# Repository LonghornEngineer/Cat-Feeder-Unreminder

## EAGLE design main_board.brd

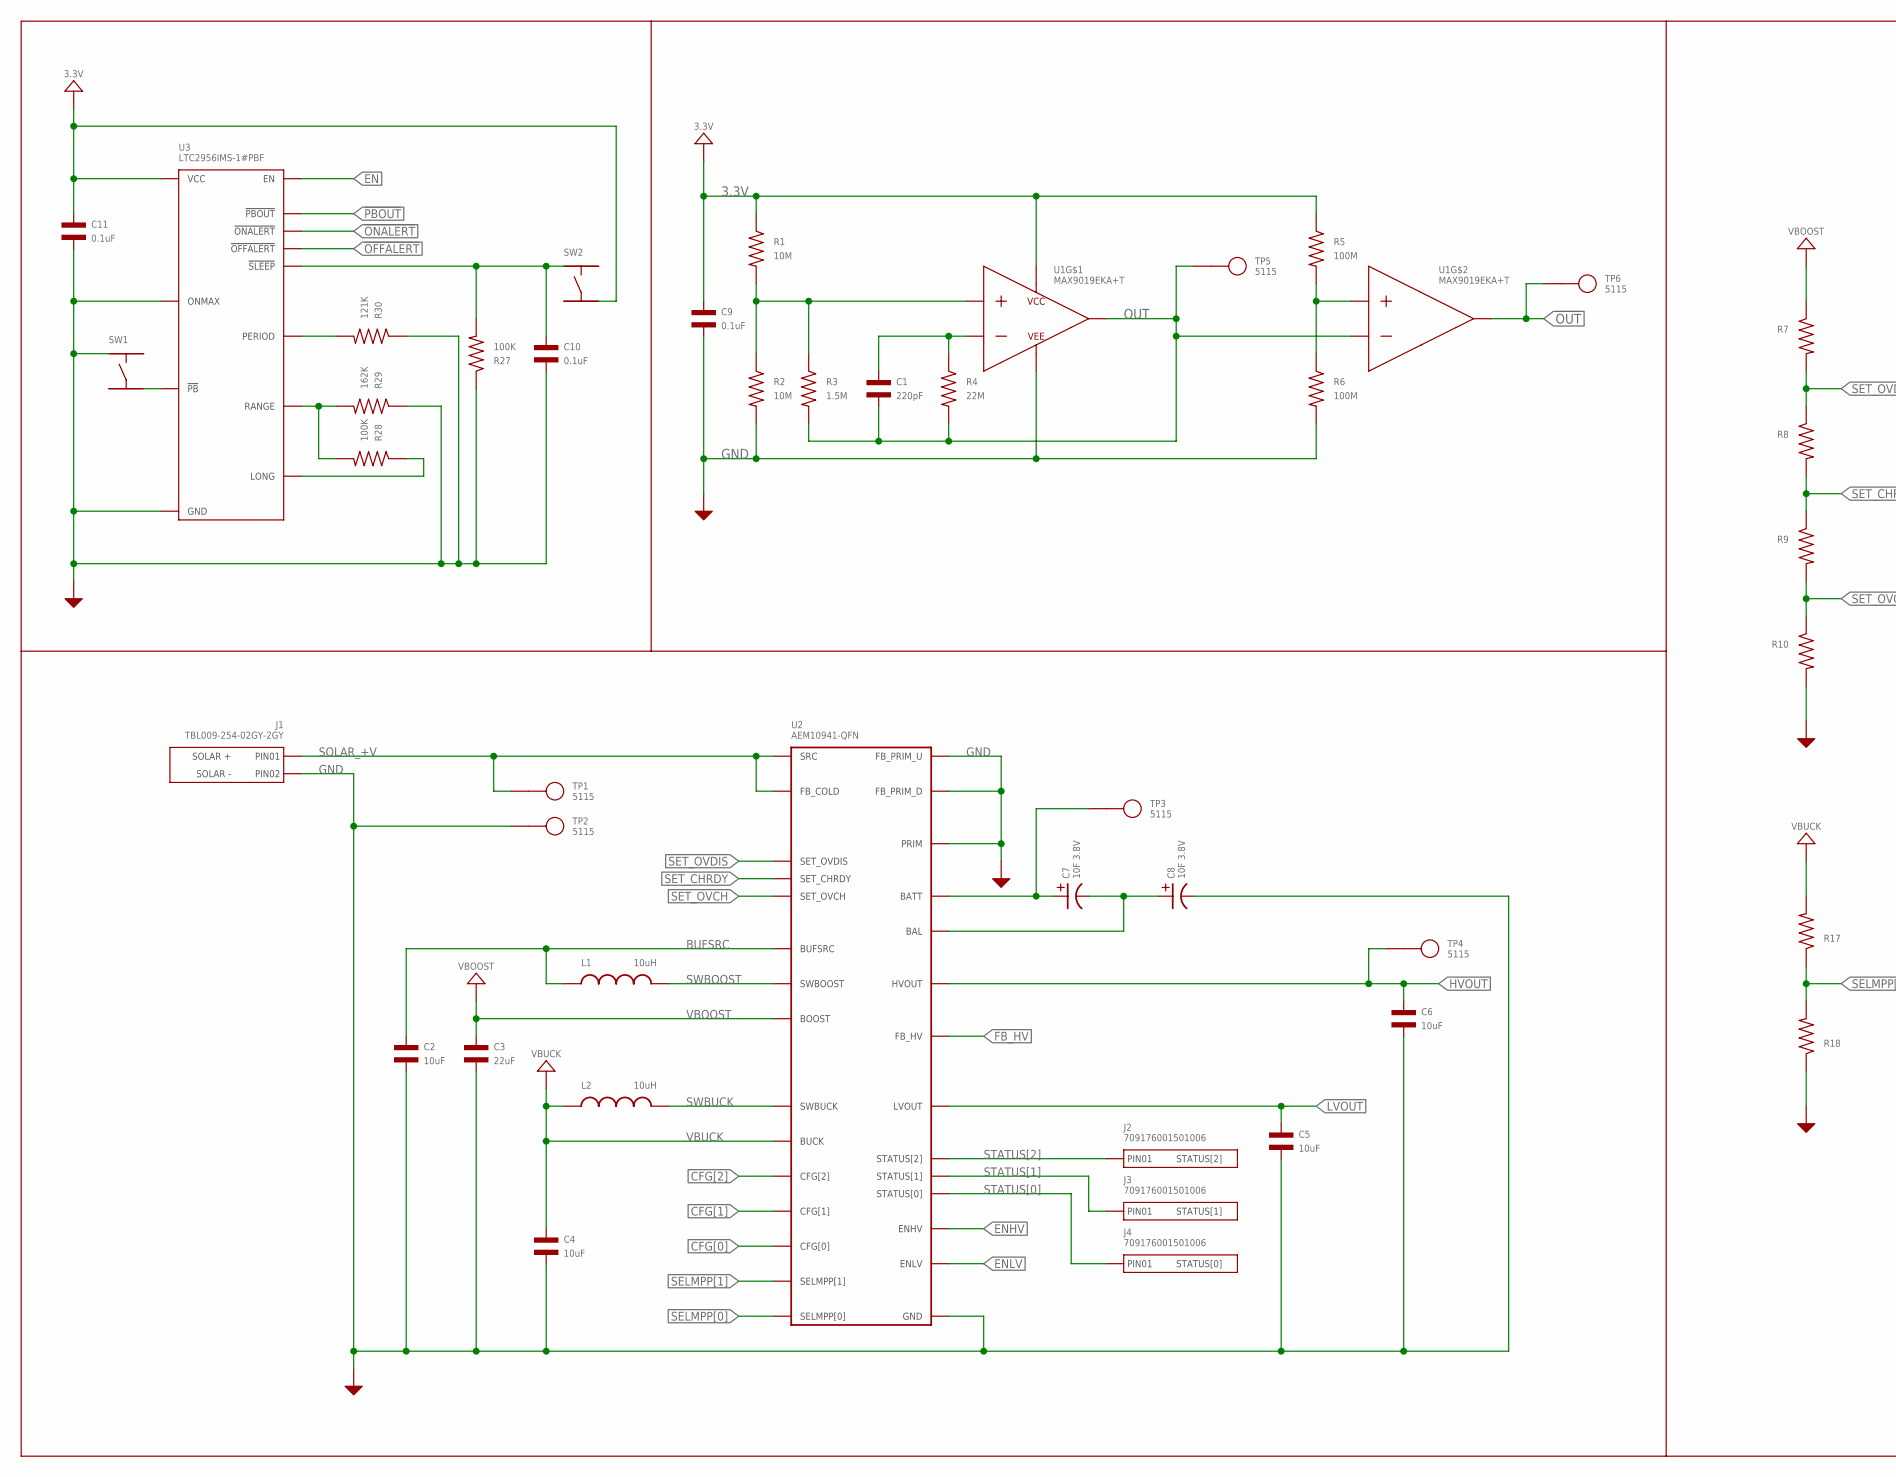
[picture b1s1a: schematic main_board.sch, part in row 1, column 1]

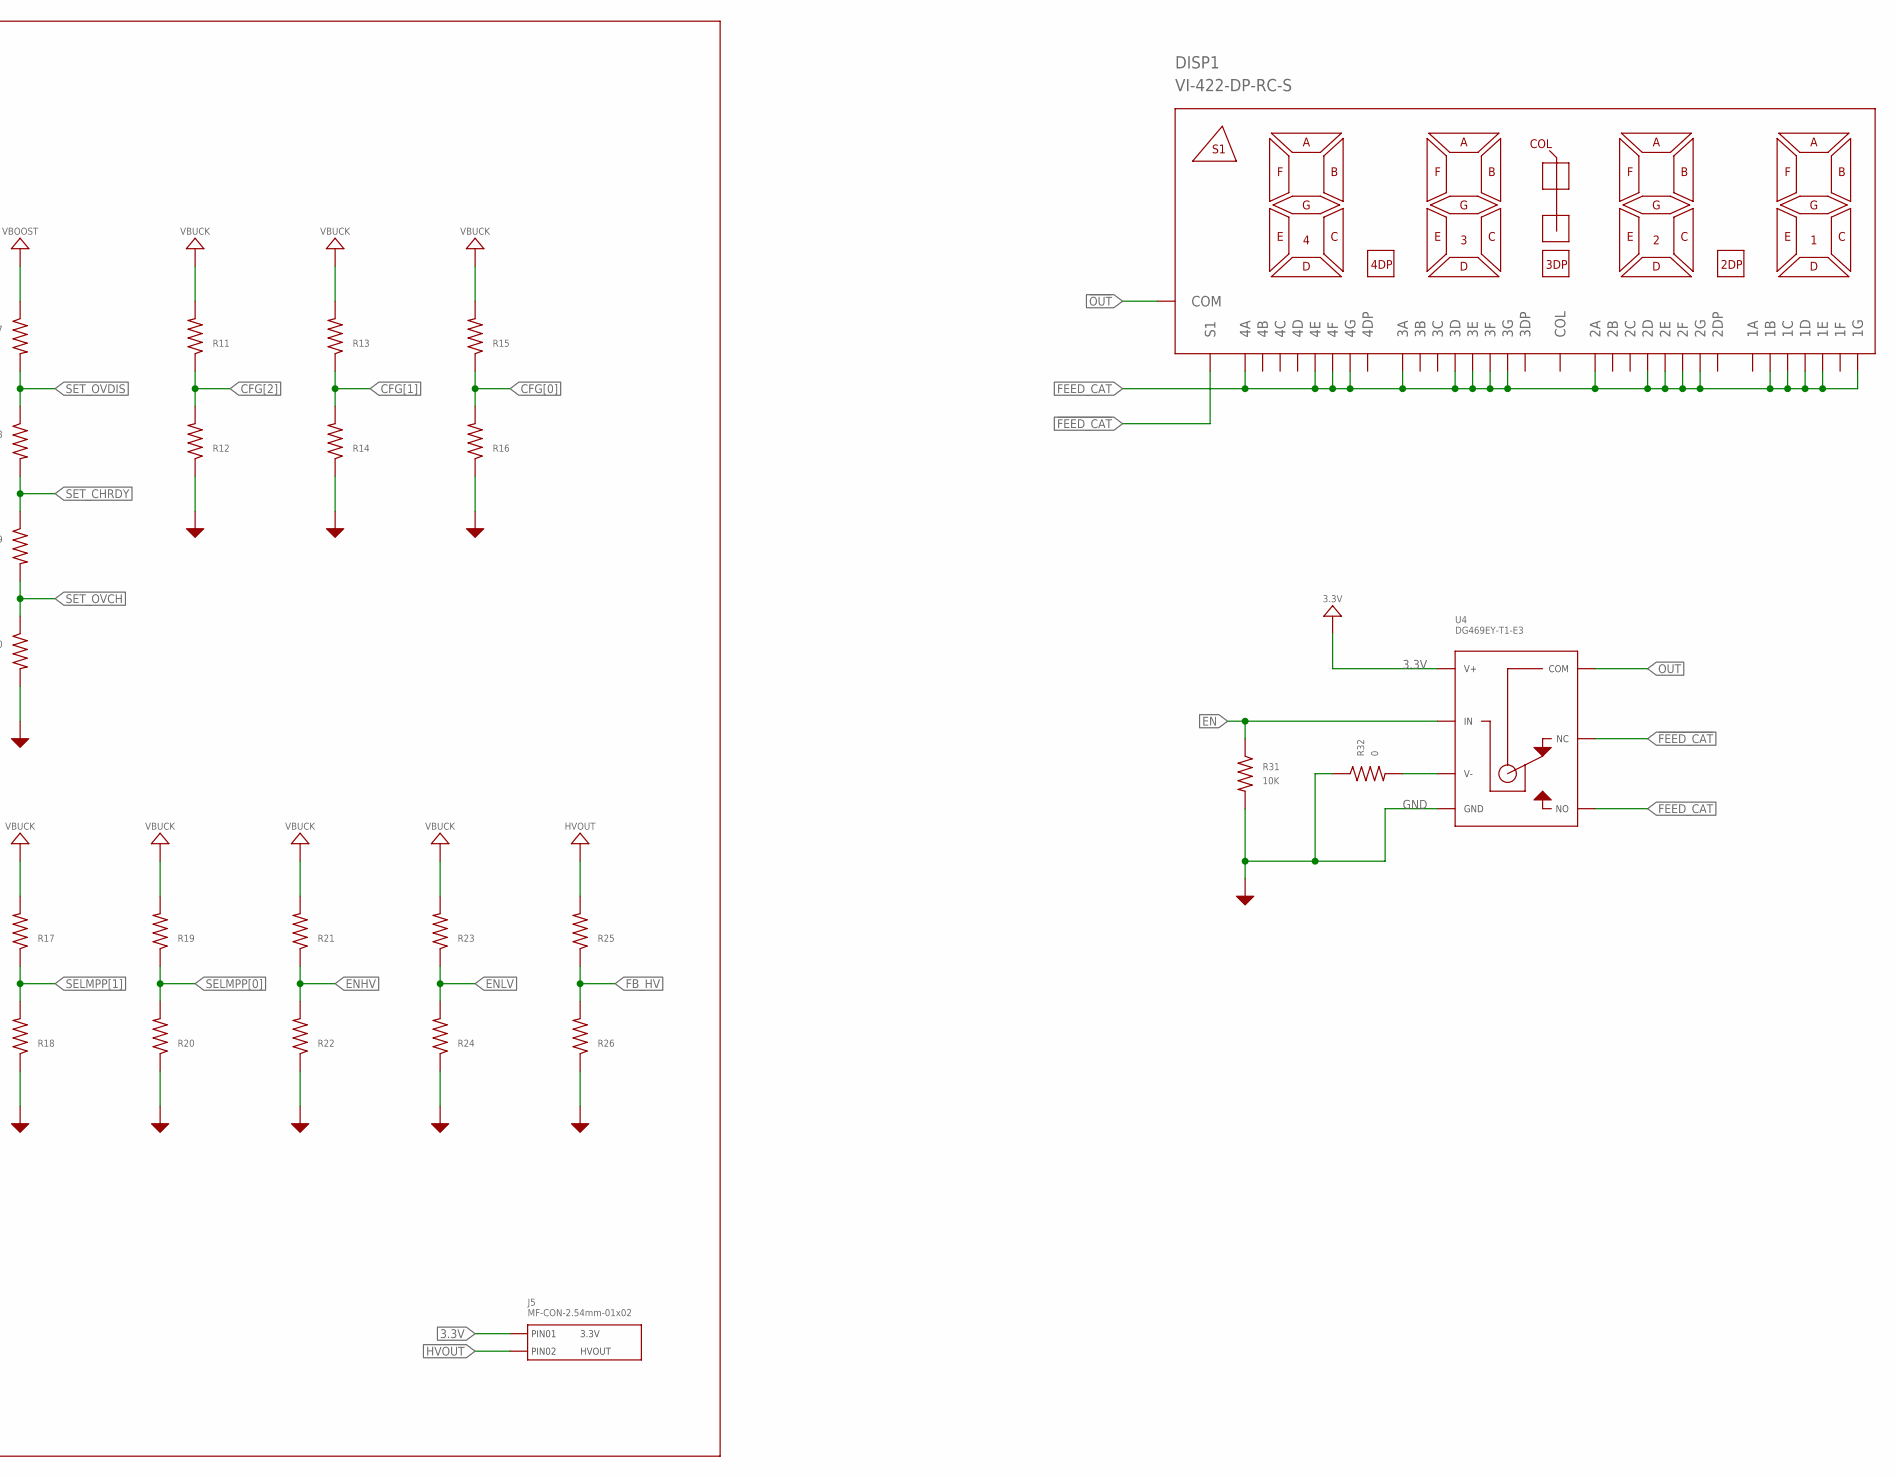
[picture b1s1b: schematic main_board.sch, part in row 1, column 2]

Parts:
C1: 220pF; C0805
C2, C4, C5, C6: 10uF; C0603; MPN C1608X5R1A106M080AC
C3: 22uF; C0603; MPN GRM188R61A226ME15D
C7, C8: 10F 3.8V; 12.5MM_CAP_PTH; MPN HSL0814-3R8106-R
C9, C10, C11: 0.1uF; C0603
DISP1: VI-422-DP-RC-S
J1: TBL009-254-02GY-2GY
J2, J3, J4: 709176001501006
J5: MF-CON-2.54mm-01x02; PTH_2.54MM_01X02
L1: 10uH; LPS4012; MPN LPS4012-103MRC
L2: 10uH; 0603; MPN MLZ1608M100WT
R1, R2: 10M; R0805
R3: 1.5M; R0805
R4: 22M; R0805
R5, R6: 100M; R0805
R7, R8, R9, R10, R11, R12, R13, R14, R15, R16, R17, R18, R19, R20, R21, R22, R23, R24, R25, R26: RESISTOR_0805; R0805
R27: 100K; R0805
R28: 100K; R0805; MPN ERA-3ARB104V
R29: 162K; R0805; MPN ERA-3AEB1623V
R30: 121K; R0805; MPN ERA-3AEB1213V
R31: 10K; R0805
R32: 0; R0805
SW1, SW2: TACT_4.2MM; TACT4.2MM; MPN PTS810 SJM 250 SMTR LFS
TP1, TP2, TP3, TP4, TP5, TP6: 5115; KEYSTONE_5115-5119
U1: MAX9019EKA+T
U2: AEM10941-QFN; AEM10941_QFN-28
U3: LTC2956IMS-1#PBF; LTC2956_MSOP-12
U4: DG469EY-T1-E3; DG469_SOIC-8

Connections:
3.3V: C9.P$1, C11.P$1, J5.P$1 (PIN1), R1.P$1, R5.P$1, SW2.P$4, U1.P$8 (VCC), U3.P$5 (VCC), U4.P$4 (V+)
!FEED_CAT: DISP1.P$38 (S1), U4.P$2 (NC)
!OFFALERT: U3.P$10 (!OFFALERT)
!ONALERT: U3.P$12 (!ONALERT)
!OUT: DISP1.P$1 (COM), DISP1.P$40 (COM), TP6.P$1, U1.P$7 (OUTPUT_2)
!PB: SW1.P$4, U3.P$7 (!PB)
!PBOUT: U3.P$9 (!PBOUT)
!SLEEP: C10.P$1, R27.P$2, SW2.P$1, U3.P$11 (!SLEEP)
BAL: C7.NEG, C8.POS, U2.P$15 (BAL)
BATT: C7.POS, TP3.P$1, U2.P$16 (BATT)
BUFSRC: C2.P$1, L1.P$2, U2.P$27 (BUFSRC)
CFG[0]: R15.P$1, R16.P$2, U2.P$6 (CFG[0])
CFG[1]: R13.P$1, R14.P$2, U2.P$5 (CFG[1])
CFG[2]: R11.P$1, R12.P$2, U2.P$4 (CFG[2])
EN: R31.P$1, U3.P$8 (EN), U4.P$6 (IN)
ENHV: R21.P$1, R22.P$2, U2.P$12 (ENHV)
ENLV: R23.P$1, R24.P$2, U2.P$18 (ENLV)
FB_HV: R25.P$1, R26.P$2, U2.P$13 (FB_HV)
FEED_CAT: DISP1.P$5 (4E), DISP1.P$9 (3E), DISP1.P$10 (3D), DISP1.P$13 (2E), DISP1.P$14 (2D), DISP1.P$17 (1E), DISP1.P$18 (1D), DISP1.P$19 (1C), DISP1.P$20 (1B), DISP1.P$23 (1G), DISP1.P$25 (2A), DISP1.P$26 (2F), DISP1.P$27 (2G), DISP1.P$30 (3A), DISP1.P$31 (3F), DISP1.P$32 (3G), DISP1.P$35 (4A), DISP1.P$36 (4F), DISP1.P$37 (4G), U4.P$8 (NO)
GND: C2.P$2, C3.P$2, C4.P$2, C5.P$2, C6.P$2, C8.NEG, C9.P$2, C10.P$2, C11.P$2, J1.2A (PIN2), J1.2B (PIN2), R2.P$2, R6.P$2, R10.P$2, R12.P$1, R14.P$1, R16.P$1, R18.P$1, R20.P$1, R22.P$1, R24.P$1, R26.P$1, R27.P$1, R29.P$1, R30.P$1, R31.P$2, R32.P$1, SW1.P$1, TP2.P$1, U1.P$4 (VEE), U2.P$9 (FB_PRIM_D), U2.P$10 (FB_PRIM_U), U2.P$17 (PRIM), U2.P$29 (GND), U3.P$1 (ONMAX), U3.P$6 (GND), U4.P$3 (GND)
HVOUT: C6.P$1, J5.P$2 (PIN2), R25.P$2, TP4.P$1, U2.P$14 (HVOUT)
LONG: R28.P$1, U3.P$2 (LONG)
LVOUT: C5.P$1, U2.P$11 (LVOUT)
unnamed: R1.P$2, R2.P$1, R3.P$1, U1.P$3 (INPUT_1+)
unnamed: R5.P$2, R6.P$1, U1.P$5 (INPUT_2+)
unnamed: C1.P$1, R4.P$1, U1.P$2 (INPUT_1-)
unnamed: R32.P$2, U4.P$7 (V-)
OUT: C1.P$2, R3.P$2, R4.P$2, TP5.P$1, U1.P$1 (OUTPUT_1), U1.P$6 (INPUT_2-), U4.P$1 (COM)
PERIOD: R30.P$2, U3.P$4 (PERIOD)
RANGE: R28.P$2, R29.P$2, U3.P$3 (RANGE)
SELMPP[0]: R19.P$1, R20.P$2, U2.P$8 (SELMPP[0])
SELMPP[1]: R17.P$1, R18.P$2, U2.P$7 (SELMPP[1])
SET_CHRDY: R8.P$2, R9.P$1, U2.P$23 (SET_CHRDY)
SET_OVCH: R9.P$2, R10.P$1, U2.P$22 (SET_OVCH)
SET_OVDIS: R7.P$2, R8.P$1, U2.P$24 (SET_OVDIS)
SOLAR_+V: J1.1A (PIN1), J1.1B (PIN1), TP1.P$1, U2.P$25 (SRC), U2.P$26 (FB_COLD)
STATUS[0]: J4.P$1, U2.P$21 (STATUS[0])
STATUS[1]: J3.P$1, U2.P$20 (STATUS[1])
STATUS[2]: J2.P$1, U2.P$19 (STATUS[2])
SWBOOST: L1.P$1, U2.P$28 (SWBOOST)
SWBUCK: L2.1, U2.P$2 (SWBUCK)
VBOOST: C3.P$1, R7.P$1, U2.P$1 (BOOST)
VBUCK: C4.P$1, L2.2, R11.P$2, R13.P$2, R15.P$2, R17.P$2, R19.P$2, R21.P$2, R23.P$2, U2.P$3 (BUCK)

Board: 2 copper layers, 63 parts (0 on the bottom side), 40 nets, no tracks yet.

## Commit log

2023-01-02 MAX9019 Oscillator Design
2023-01-03 uploading for article
2023-01-06 working on the solar circuit
2023-01-10 AEM10941 circuit complete
2023-01-15 timer implemented in schematic
2023-01-20 Added analog switch
